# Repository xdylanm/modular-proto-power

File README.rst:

Prototype Power
===============

A module in the Eurorack format that provides power pins and basic signals for prototyping.

Features
--------

Power Headers
^^^^^^^^^^^^^

Power headers are broken out at the front panel

* 16P IDC connector with Eurorack "standard" pinout for power distribution 

    * Reference: https://division-6.com/learn/eurorack-power/
    * Use keyed IDC connectors and housings and associate -12V with pin 1. Ensure cables are oriented correctly (red stripe to pin 1).

* 1x3 headers for +12V, +5V, ground, and -12V

*Note*: Doepfer, who started the mess of using ribbon cables and IDC connectors for power distribution, explicitly avoids keyed housings for the connectors in favour of open 2x8 pin headers (https://doepfer.de/a100_man/a100t_e.htm). In this case, you are expected to rely on board markings or, worse, location of the header on the PCB, to determine the orientation. This is dumb. It's straightforward to confirm that the cable orientation matches the keying on the connectors (check both ends and any mid-cable connectors), which ultimately makes assembly and connection simpler.

Buffers/DC Outputs
^^^^^^^^^^^^^^^^^^

Two buffers are provided. The input of the second is normaled to the input of the first, enabling signal duplication.

* The first buffer is connected internally to a DC input with an adjustable :math:`\pm 10V` range. That connection is broken when the external input for buffer 1 is used.
* The input for the second buffer is connected internally (normaled) to the input for the first. That connection is broken when the external input for buffer 2 is used.

Gate and Envelope Generator
^^^^^^^^^^^^^^^^^^^^^^^^^^^

A 5V gate signal can be generated in one-shot (push button) or oscillator mode. Both the pulse length and frequency can be adjusted. The gate signal is also fed into a simple AR envelope with controls for attack and release, and the envelope is output.

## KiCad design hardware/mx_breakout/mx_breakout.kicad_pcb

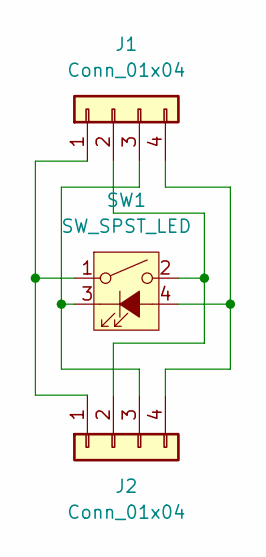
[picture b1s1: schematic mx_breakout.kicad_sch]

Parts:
J1, J2: Conn_01x04; PinHeader_1x04_P2.54mm_Vertical
SW1: SW_SPST_LED; SW_Cherry_MX_1.00u_LED_PCB

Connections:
unnamed: J1.1, J2.1, SW1.1
unnamed: J1.2, J2.2, SW1.2
unnamed: J1.3, J2.3, SW1.3 (K)
unnamed: J1.4, J2.4, SW1.4 (A)

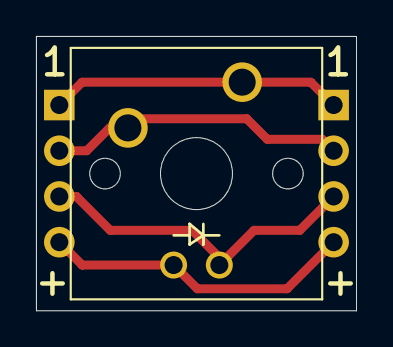
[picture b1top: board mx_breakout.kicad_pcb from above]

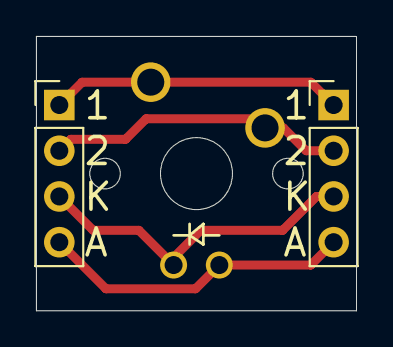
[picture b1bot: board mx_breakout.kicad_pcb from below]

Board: 2 copper layers, 17.8 x 15.2 mm, 3 parts (2 on the bottom side), 4 nets.

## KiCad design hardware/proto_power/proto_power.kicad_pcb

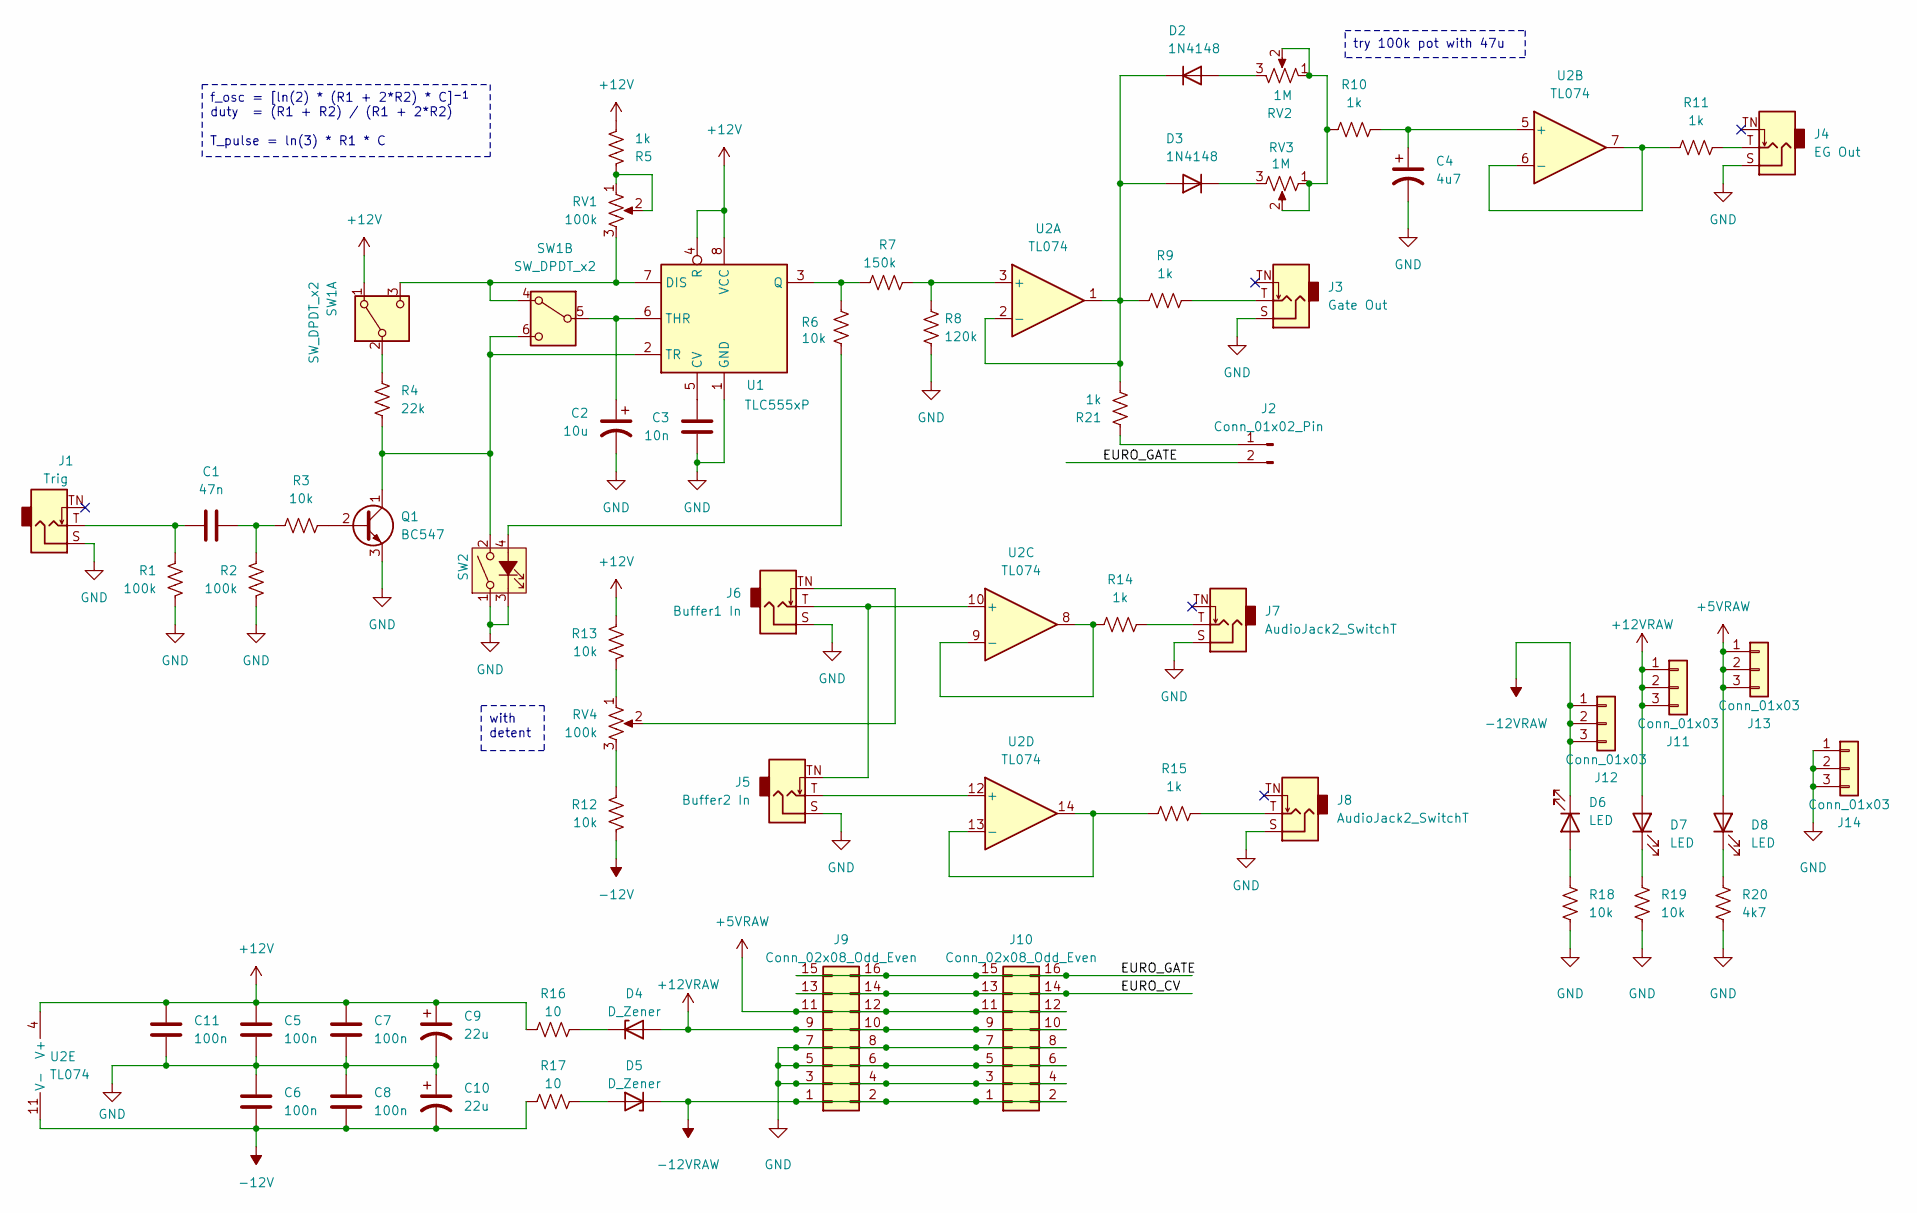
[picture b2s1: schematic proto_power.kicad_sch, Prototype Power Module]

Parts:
C1: 47n; C_Disc_D4.7mm_W2.5mm_P5.00mm
C2: 10u; CP_Radial_D4.0mm_P2.00mm
C3: 10n; C_Disc_D4.7mm_W2.5mm_P5.00mm
C4: 4u7; CP_Radial_D4.0mm_P2.00mm
C5, C6, C7, C8, C11: 100n; C_Disc_D4.7mm_W2.5mm_P5.00mm
C9, C10: 22u; CP_Radial_D5.0mm_P2.50mm
D2, D3: 1N4148; D_DO-35_SOD27_P7.62mm_Horizontal
D4, D5: D_Zener; D_DO-41_SOD81_P7.62mm_Horizontal
D6, D7, D8: LED; LED_D3.0mm
J1: Trig; Jack_3.5mm_QingPu_WQP-PJ301M-12_Vertical
J2: Conn_01x02_Pin; PinHeader_1x02_P2.54mm_Vertical
J3: Gate Out; Jack_3.5mm_QingPu_WQP-PJ301M-12_Vertical
J4: EG Out; Jack_3.5mm_QingPu_WQP-PJ301M-12_Vertical
J5: Buffer2 In; Jack_3.5mm_QingPu_WQP-PJ301M-12_Vertical
J6: Buffer1 In; Jack_3.5mm_QingPu_WQP-PJ301M-12_Vertical
J7, J8: AudioJack2_SwitchT; Jack_3.5mm_QingPu_WQP-PJ301M-12_Vertical
J9, J10: Conn_02x08_Odd_Even; IDC-Header_2x08_P2.54mm_Vertical
J11, J12, J13, J14: Conn_01x03; PinSocket_1x03_P2.54mm_Vertical
Q1: BC547; TO-92_Inline_Wide
R1, R2: 100k; R_Axial_DIN0204_L3.6mm_D1.6mm_P2.54mm_Vertical
R3, R6, R18, R19: 10k; R_Axial_DIN0204_L3.6mm_D1.6mm_P2.54mm_Vertical
R4: 22k; R_Axial_DIN0204_L3.6mm_D1.6mm_P2.54mm_Vertical
R5, R9, R10, R15: 1k; R_Axial_DIN0204_L3.6mm_D1.6mm_P2.54mm_Vertical
R7: 150k; R_Axial_DIN0204_L3.6mm_D1.6mm_P2.54mm_Vertical
R8: 120k; R_Axial_DIN0204_L3.6mm_D1.6mm_P2.54mm_Vertical
R11, R14, R21: 1k; R_Axial_DIN0204_L3.6mm_D1.6mm_P7.62mm_Horizontal
R12, R13: 10k; R_Axial_DIN0204_L3.6mm_D1.6mm_P7.62mm_Horizontal
R16, R17: 10; R_Axial_DIN0204_L3.6mm_D1.6mm_P2.54mm_Vertical
R20: 4k7; R_Axial_DIN0204_L3.6mm_D1.6mm_P2.54mm_Vertical
RV1, RV4: 100k; Potentiometer_Bourns_PTV09A-1_Single_Vertical
RV2, RV3: 1M; Potentiometer_Bourns_PTV09A-1_Single_Vertical
SW1: SW_DPDT_x2; SW_DPDT_13mm_x_13mm_P5.00mm
SW2: SW_SPST_LED; SW_Cherry_MX_1.00u_Breakout
U1: TLC555xP; DIP-8_W7.62mm_Socket
U2: TL074; DIP-14_W7.62mm_Socket

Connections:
+5VRAW: D8.2 (A), J9.11, J9.12, J10.11, J10.12, J13.1, J13.2, J13.3
+12V: C5.1, C7.1, C9.1, C11.1, R5.2, R13.2, R16.1, SW1.1 (A), U1.4 (R), U1.8 (VCC), U2.4 (V+)
+12VRAW: D4.2 (A), D7.2 (A), J9.9, J9.10, J10.9, J10.10, J11.1, J11.2, J11.3
-12V: C6.2, C8.2, C10.2, R12.1, R17.1, U2.11 (V-)
-12VRAW: D5.1 (K), D6.1 (K), J9.1, J9.2, J10.1, J10.2, J12.1, J12.2, J12.3
/EURO_CV: J9.13, J9.14, J10.13, J10.14
/EURO_GATE: J2.2, J9.15, J9.16, J10.15, J10.16
GND: C2.2, C3.2, C4.2, C5.2, C6.1, C7.2, C8.1, C9.2, C10.1, C11.2, J1.S, J3.S, J4.S, J5.S, J6.S, J7.S, J8.S, J9.3, J9.4, J9.5, J9.6, J9.7, J9.8, J10.3, J10.4, J10.5, J10.6, J10.7, J10.8, J14.1, J14.2, J14.3, Q1.3 (E), R1.2, R2.2, R8.2, R18.2, R19.2, R20.2, SW2.1, SW2.3 (K), U1.1 (GND)
unnamed: C1.1, J1.T, R1.1
unnamed: C1.2, R2.1, R3.2
unnamed: D2.2 (A), RV2.3
unnamed: D2.1 (K), D3.2 (A), R9.1, R21.1, U2.1, U2.2 (-)
unnamed: D3.1 (K), RV3.3
unnamed: D4.1 (K), R16.2
unnamed: D5.2 (A), R17.2
unnamed: D6.2 (A), R18.1
unnamed: D7.1 (K), R19.1
unnamed: D8.1 (K), R20.1
unnamed: J2.1, R21.2
unnamed: J3.T, R9.2
unnamed: J4.T, R11.2
unnamed: J6.TN, RV4.2
unnamed: J7.T, R14.2
unnamed: J8.T, R15.2
unnamed: Q1.2 (B), R3.1
unnamed: Q1.1 (C), R4.2, SW1.6 (C), SW2.2, U1.2 (TR)
unnamed: R5.1, RV1.1, RV1.2
unnamed: R10.1, RV2.1, RV2.2, RV3.1, RV3.2
unnamed: R12.2, RV4.3
unnamed: R13.1, RV4.1
unnamed: R4.1, SW1.2 (B)
unnamed: RV1.3, SW1.3 (C), SW1.4 (A), U1.7 (DIS)
unnamed: C2.1, SW1.5 (B), U1.6 (THR)
unnamed: R6.1, SW2.4 (A)
unnamed: C3.1, U1.5 (CV)
unnamed: R6.2, R7.1, U1.3 (Q)
unnamed: R7.2, R8.1, U2.3 (+)
unnamed: C4.1, R10.2, U2.5 (+)
unnamed: R11.1, U2.6 (-), U2.7
unnamed: J5.TN, J6.T, U2.10 (+)
unnamed: R14.1, U2.8, U2.9 (-)
unnamed: J5.T, U2.12 (+)
unnamed: R15.1, U2.13 (-), U2.14

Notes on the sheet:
try 100k pot with 47u
with detent
f_osc = [ln(2) * (R1 + 2*R2) * C]^{-1} duty = (R1 + R2) / (R1 + 2*R2) T_pulse = ln(3) * R1 * C

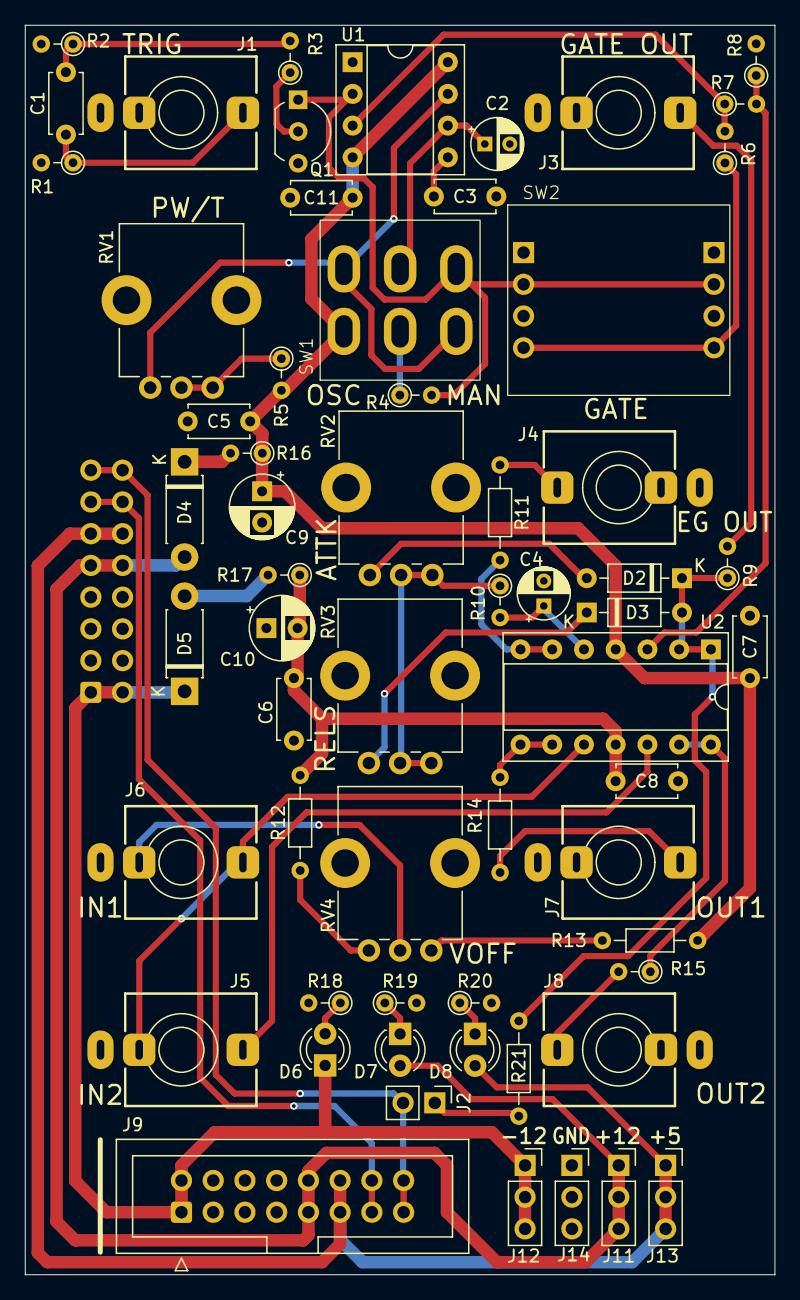
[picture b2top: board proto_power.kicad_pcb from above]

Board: 2 copper layers, 60.0 x 100.0 mm, 62 parts (1 on the bottom side), 43 nets.

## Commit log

2025-02-16 Initial design for a prototyping power module. See README for details
2025-03-03 v1 board released for mfg.

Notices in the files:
hardware/proto_power/proto_power.kicad_pcb:
idyllm CC BY-SA 4.0
hardware/proto_power/proto_power.kicad_sch:
CC BY-SA 4.0
